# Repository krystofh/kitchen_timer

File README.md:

# Kitchen timer

Kitchen timer based on 4-digit 8-segment display 3461BS and RP Pico

||
|-|
|**Front view of the PCB**|

||
|-|
|**Back view of the PCB**|

## Electronics

The used display is a common anode display. The datasheet specifies 10 mA typical current for the optical characteristics of a segment. The GPIOs of RP Pico can provide 12 mA max. The built-in `3V3OUT` voltage regulator can output up to 300 mA, which is sufficient for all 8 segemts. Not the full 32 segments are needed since the digits are displayed with a given refresh rate sequentially once at a time. Simulation using LTSpice and PNP transistor `BCS327-25` leads to the choice of resistor value

s with 220 Ohm and 22k. For the edge cases "1 segment" and "8 segments" the current limitations are fulfilled.

## Zephyr RTOS

### Setting PWM on a pin

1.  Start by enabling PWM in the `prj.conf` file: `CONFIG_PWM=y`
2.  In the `.overlay` file, enable the node `pwm_led0` by setting the status:
    ```c
    &pwm_led0 {
	status = "okay";
    };
    ```
3. Check the PWM generator corresponding to the GPIO. For RP Pico, these are:

    It results in a table:
    |PWM channel Nr.|PWM channel| GPIO|
    |-|-|-|
    |0|0A|0|
    |1|0B|1|
    |2|1A|2|
    |..|..|..|
    |15|7B|15|
    |0 ❗|0A|16|
    |1|0B|17|

    This means that to set PWM ON GPIO 27, we will need `PWM 5B` with the number `11`.

4. In the `.dts` file (not the overlay!), edit the `pwm_leds` node:
   ```c
    pwm_leds {
		compatible = "pwm-leds";
		status = "disabled";
		pwm_led0: pwm_led_0 {
			pwms = <&pwm 11 PWM_MSEC(20) PWM_POLARITY_NORMAL>;
			label = "PWM_LED";
		};
	};
   ```
5. Next, set the PWM on the specific pin. In the `rpi_pico-common.dtsi`:
   ```c
    &pwm {
	pinctrl-0 = <&pwm_ch5b_default>;
	pinctrl-names = "default";
    };
   ```
6. Finally, add the pinmux in `rpi_pico-pinctrl.dtsi` for GPIO 27:
   ```c
   pwm_ch5b_default: pwm_ch5b_default {
		group1 {
			pinmux = <PWM_5B_P27>;
		};
	};
   ```
7. Follow the examples such as [PWM Blinky](https://docs.zephyrproject.org/latest/samples/basic/blinky_pwm/README.html#pwm-blinky) and compile them with the changed devicetree. If it works, start coding your own application.

## Device tree definitions

Device tree nodes are aliased like in the picture below. The change from `-` to `_` is mandatory!

In the `.c` code, the alias is used like:

```c
static const struct pwm_dt_spec my_variable = PWM_DT_SPEC_GET(DT_ALIAS(buzzer_dev));
```
 
## Links

- 
- https://www.electronics-tutorials.ws/blog/7-segment-display-tutorial.html
- https://www.instructables.com/12-Pin-7-Segment-Display-Wiring-Tutorial/
- https://www.reddit.com/r/AskElectronics/comments/oti47u/what_is_the_purpose_of_the_transistors_when_using/
- https://www.youtube.com/watch?v=sKJuzInKj_M
- https://www.youtube.com/watch?v=256VQ6eVNng
- https://www.youtube.com/watch?v=Fa7BHbPAM98

- Switch debouncing https://zephyrproject.org/how-to-debounce-button-inputs-in-a-rtos/
- PWM https://blog.golioth.io/adding-pwm-sound-in-zephyr/

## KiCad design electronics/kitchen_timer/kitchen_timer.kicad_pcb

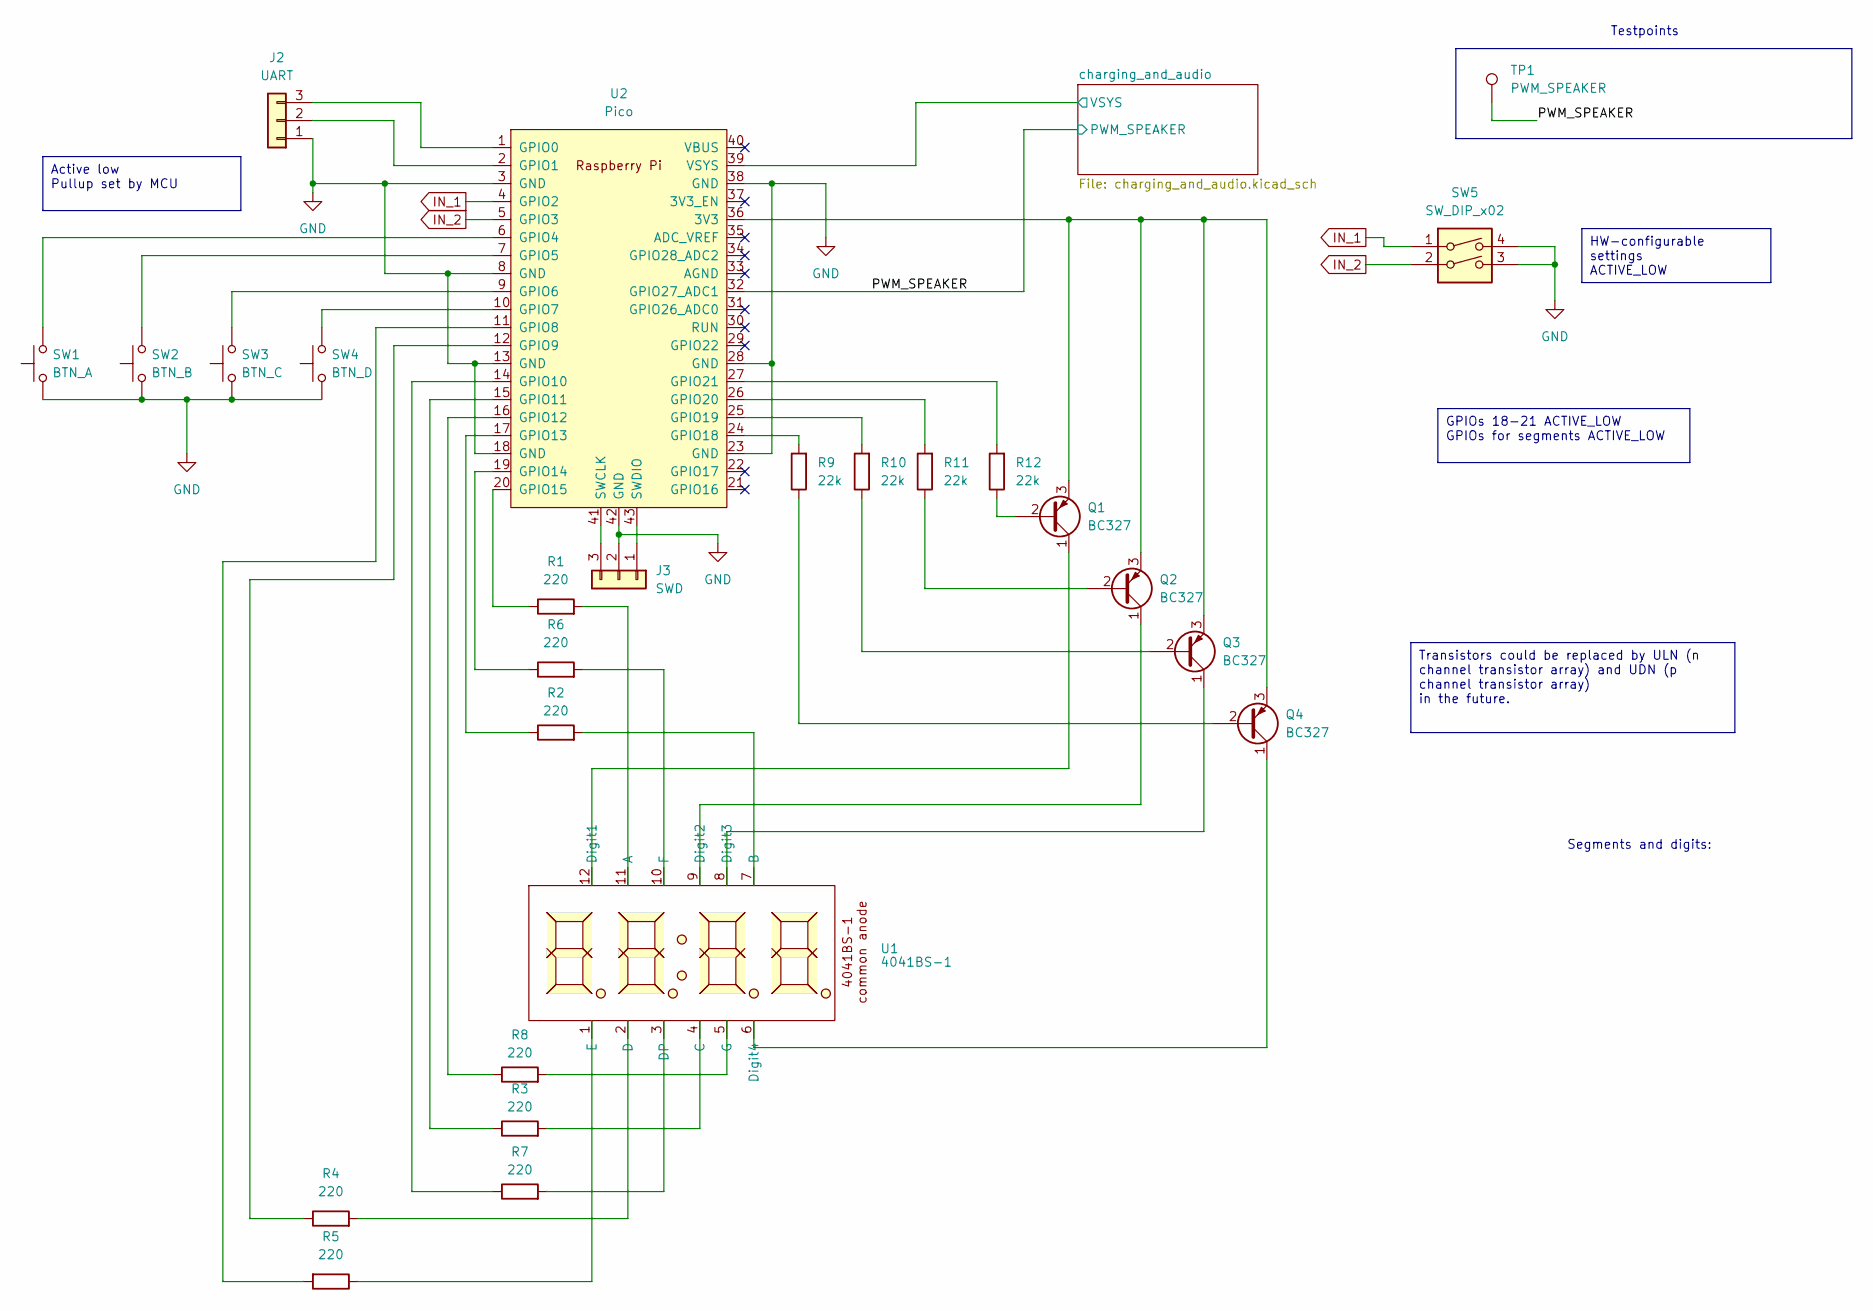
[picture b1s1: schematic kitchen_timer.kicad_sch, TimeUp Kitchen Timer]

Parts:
J2: UART; PinHeader_1x03_P2.54mm_Horizontal
J3: SWD; PinSocket_1x03_P2.54mm_Horizontal
Q1, Q2, Q3, Q4: BC327; TO-92_Inline
R1, R2, R3, R4, R5, R6, R7, R8: 220; R_Axial_DIN0207_L6.3mm_D2.5mm_P10.16mm_Horizontal
R9, R10, R11, R12: 22k; R_Axial_DIN0207_L6.3mm_D2.5mm_P10.16mm_Horizontal
SW1: BTN_A; SW_PUSH_6mm_H4.3mm
SW2: BTN_B; SW_PUSH_6mm_H4.3mm
SW3: BTN_C; SW_PUSH_6mm_H4.3mm
SW4: BTN_D; SW_PUSH_6mm_H4.3mm
SW5: SW_DIP_x02; DIP-4_W7.62mm_LongPads
TP1: PWM_SPEAKER; TestPoint_Pad_2.0x2.0mm
U1: 4041BS-1; Segment_display_4041BS-1
U2: Pico; RPi_Pico_SMD_TH

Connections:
/PWM_SPEAKER: TP1.1, U2.32 (GPIO27_ADC1); also elsewhere on the board
GND: J2.1, J3.2, SW1.1, SW2.1, SW3.1, SW4.1, SW5.3, SW5.4, U2.3 (GND), U2.8 (GND), U2.13 (GND), U2.18 (GND), U2.23 (GND), U2.28 (GND), U2.38 (GND), U2.42 (GND); also elsewhere on the board
IN_1: SW5.1, U2.4 (GPIO2)
IN_2: SW5.2, U2.5 (GPIO3)
unnamed: J2.2, U2.2 (GPIO1)
unnamed: J2.3, U2.1 (GPIO0)
unnamed: J3.1, U2.43 (SWDIO)
unnamed: J3.3, U2.41 (SWCLK)
unnamed: Q1.2 (B), R12.1
unnamed: Q1.1 (C), U1.12 (Digit1)
unnamed: Q1.3 (E), Q2.3 (E), Q3.3 (E), Q4.3 (E), U2.36 (3V3)
unnamed: Q2.2 (B), R11.1
unnamed: Q2.1 (C), U1.9 (Digit2)
unnamed: Q3.2 (B), R10.1
unnamed: Q3.1 (C), U1.8 (Digit3)
unnamed: Q4.2 (B), R9.1
unnamed: Q4.1 (C), U1.6 (Digit4)
unnamed: R1.2, U1.11 (A)
unnamed: R2.2, U1.7 (B)
unnamed: R3.2, U1.4 (C)
unnamed: R4.2, U1.2 (D)
unnamed: R7.2, U1.3 (DP)
unnamed: R5.1, U1.1 (E)
unnamed: R6.2, U1.10 (F)
unnamed: R8.2, U1.5 (G)
unnamed: SW1.2, U2.6 (GPIO4)
unnamed: SW2.2, U2.7 (GPIO5)
unnamed: SW3.2, U2.9 (GPIO6)
unnamed: SW4.2, U2.10 (GPIO7)
unnamed: R5.2, U2.11 (GPIO8)
unnamed: R4.1, U2.12 (GPIO9)
unnamed: R7.1, U2.14 (GPIO10)
unnamed: R3.1, U2.15 (GPIO11)
unnamed: R8.1, U2.16 (GPIO12)
unnamed: R2.1, U2.17 (GPIO13)
unnamed: R6.1, U2.19 (GPIO14)
unnamed: R1.1, U2.20 (GPIO15)
unnamed: R9.2, U2.24 (GPIO18)
unnamed: R10.2, U2.25 (GPIO19)
unnamed: R11.2, U2.26 (GPIO20)
unnamed: R12.2, U2.27 (GPIO21)

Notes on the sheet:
Active low Pullup set by MCU
Transistors could be replaced by ULN (n channel transistor array) and UDN (p channel transistor array) in the future.
HW-configurable settings ACTIVE_LOW
GPIOs 18-21 ACTIVE_LOW GPIOs for segments ACTIVE_LOW
Segments and digits:
Testpoints

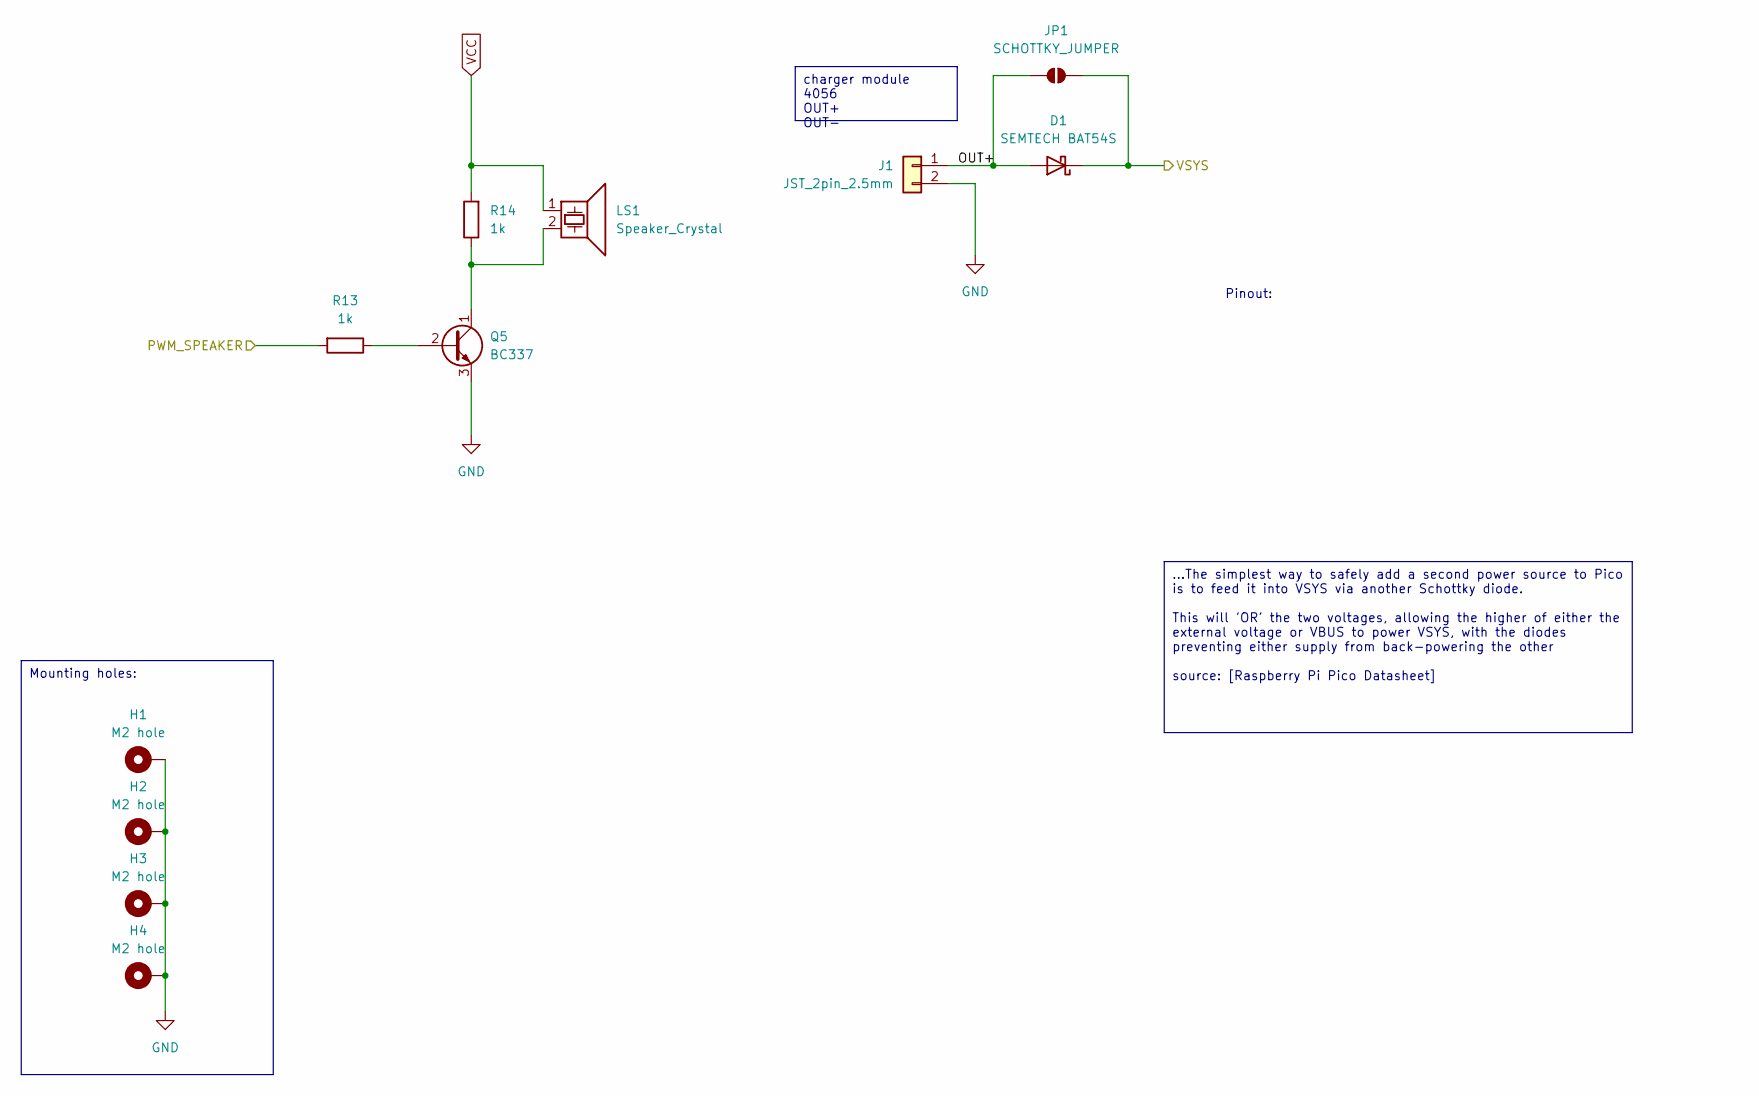
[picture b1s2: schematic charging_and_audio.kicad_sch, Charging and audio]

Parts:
D1: SEMTECH BAT54S; SOT-23_Handsoldering_renumbered
H1, H2, H3, H4: M2 hole; MountingHole_2.2mm_M2_Pad_Via
J1: JST_2pin_2.5mm; JST_2pin_2.54mm_female
JP1: SCHOTTKY_JUMPER; SolderJumper-2_P1.3mm_Open_TrianglePad1.0x1.5mm
LS1: Speaker_Crystal; Piezzo_10mm_6.5mm_combined
Q5: BC337; TO-92L_Inline_Wide
R13, R14: 1k; R_Axial_DIN0207_L6.3mm_D2.5mm_P10.16mm_Horizontal

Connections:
/PWM_SPEAKER: R13.2; also elsewhere on the board
GND: H1.1, H2.1, H3.1, H4.1, J1.2, Q5.3 (E); also elsewhere on the board
unnamed: Q5.2 (B), R13.1
unnamed: LS1.2, Q5.1 (C), R14.1
VCC: LS1.1, R14.2

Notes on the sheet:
...The simplest way to safely add a second power source to Pico is to feed it into VSYS via another Schottky diode. This will 'OR' the two voltages, allowing the higher of either the external voltage or VBUS to power VSYS, with the diodes preventing either supply from back-powering the other source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
Mounting holes:
charger module 4056 OUT+ OUT-
Pinout:

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
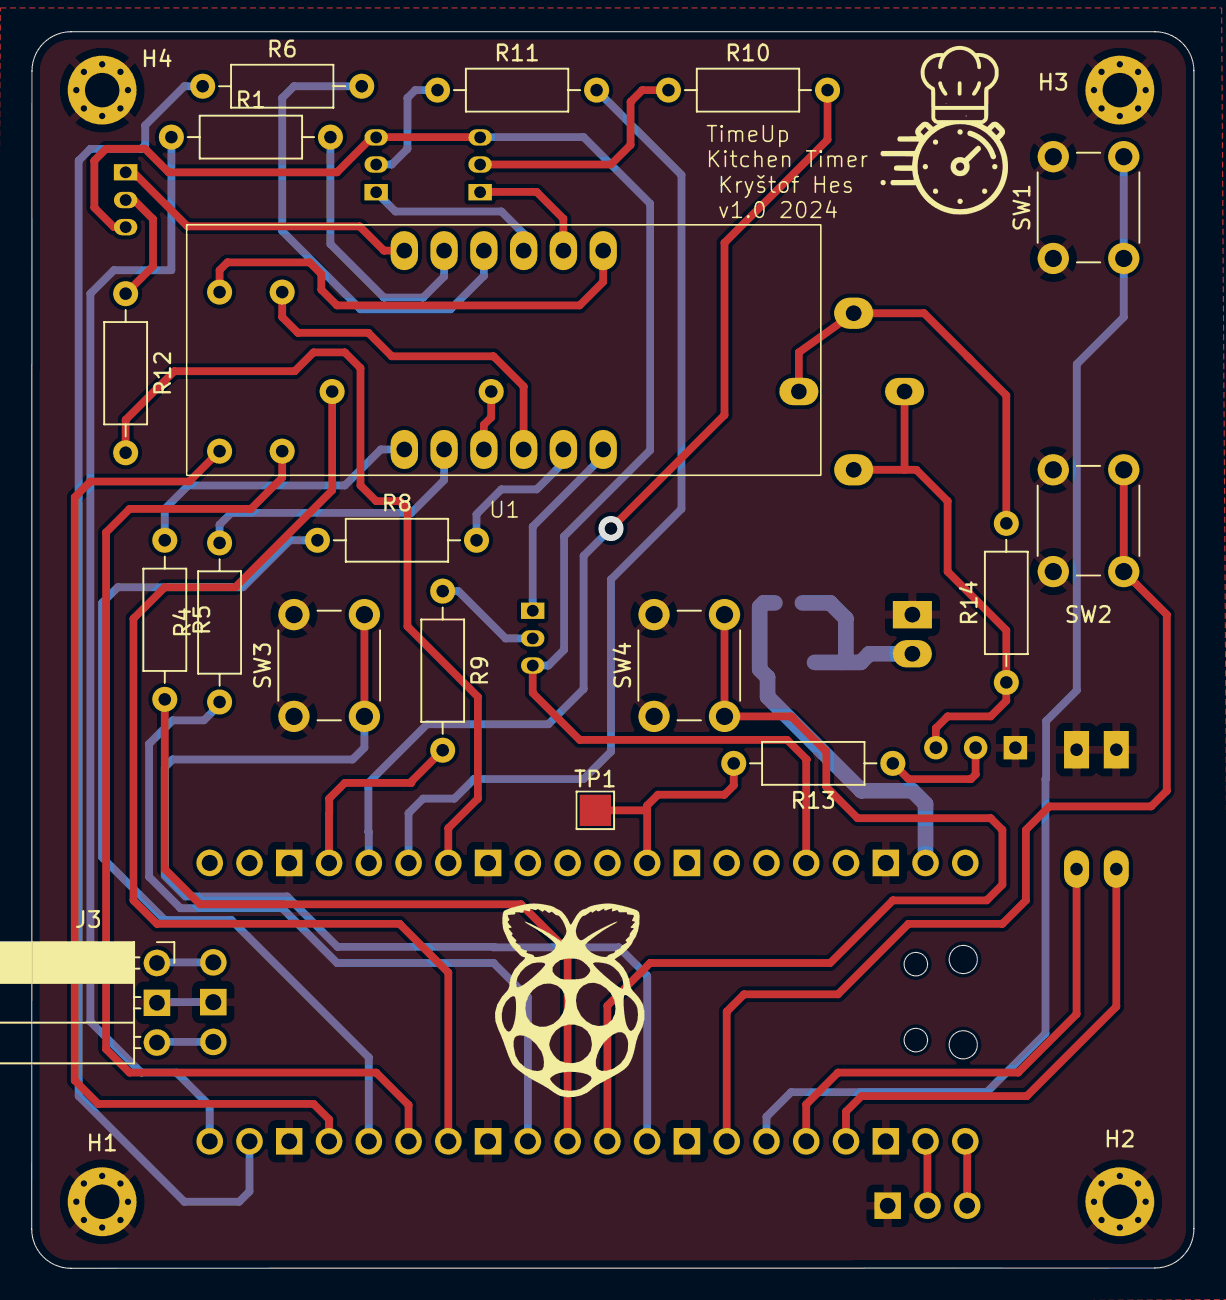
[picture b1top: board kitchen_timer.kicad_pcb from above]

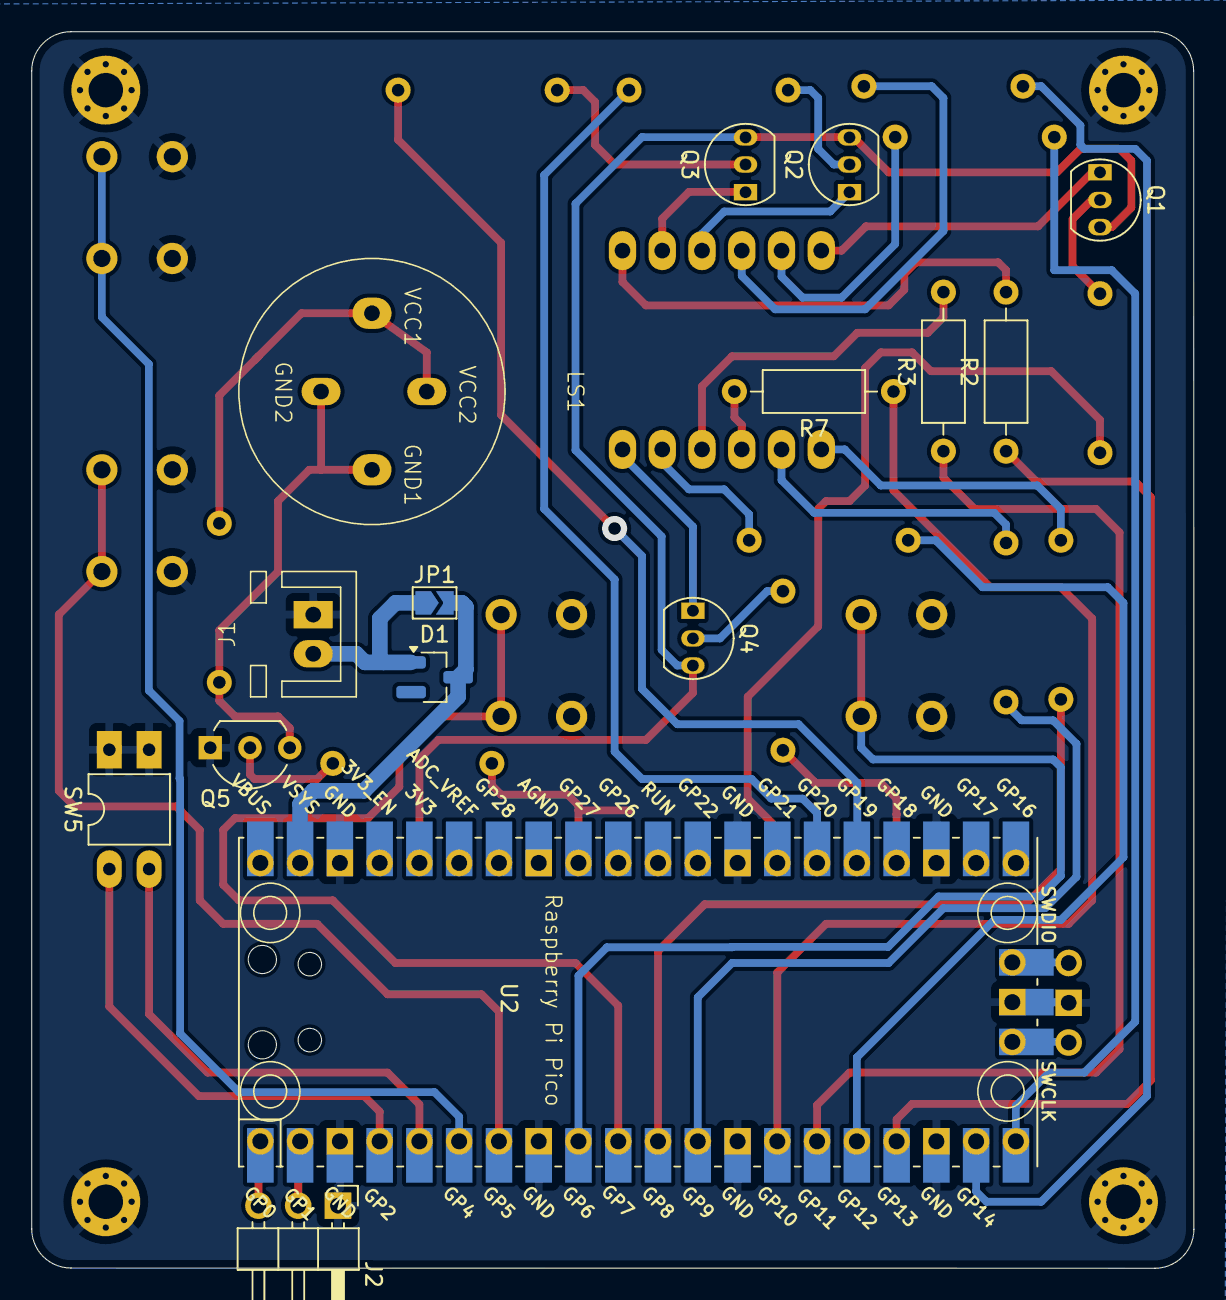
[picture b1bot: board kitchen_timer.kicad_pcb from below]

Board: 2 copper layers, 74.2 x 79.0 mm, 37 parts (15 on the bottom side), 46 nets.

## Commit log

2024-10-16 empty west repo for rp pico
2024-10-16 rewritten as free-standing app
2024-10-16 prepared device tree
2024-10-16 minimal working example of button A
2024-10-16 minimal working example with events from btn A and B
2024-10-16 prepared demo of display
2024-10-21 display demo
2024-10-21 displaying digits on all 4 positions
2024-10-21 display refresh
2024-10-21 added buttons C and D for future minute and second selection
2024-10-22 time increment and decrement without debounce
2024-10-23 button debounce partly working
2024-10-23 device tree and electronics explanations
2024-10-24 buzzer showcase
2024-11-07 sound engineering draft
2024-11-07 refactoring sound and time
2024-11-07 corrected time pointers, added reset cmd
2024-11-07 start command
2024-11-07 timer min example
2024-11-07 refactor timer as separate file from event handler
2024-11-07 countdown running per command
2024-11-07 added start stop reset sounds
2024-11-07 stop sound
2024-11-08 sound events queue, click sound
2024-11-08 note names, config of sound event queue size and no stop sound when alarm
2024-11-08 alarm loop until button pressed
2024-11-16 change VID and PID and product
2024-11-20 Add debounce for all buttons
2024-11-20 Change logic to minutes first
    Pressing btn A will first enter minute setting mode
2024-11-20 Add longpress implementation as mockup
2024-11-20 Change button C function
    C can start and stop timer
    C can reset timer on longpress
2024-11-20 Add longpress config in prj.conf
2024-11-27 Remove electronics from gitignore
2024-11-27 add electronics files
2024-11-27 Update gitignore for zip files
2024-11-27 Add 3d models to components, small rerouting
2024-12-05 Update electronics
    - added Schottky diode and solder bridge
    - corrected all errors from design rules checker
    - added silk screen logos
2024-12-07 Update electronics
    - resistors with longer spacing between holes
    - GND for SWD
    - solder jumper new footprint
    - increase distances between nets
    - added datasheet for schottky
2025-01-14 add:gerber files export to JLCPCB
2025-01-30 chore: add notes on needed fixes
